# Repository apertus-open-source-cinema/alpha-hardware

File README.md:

alpha-hardware
==============

Axiom Alpha prototype hardware source files (electronic schematics, documentation, PCB layouts, etc.)

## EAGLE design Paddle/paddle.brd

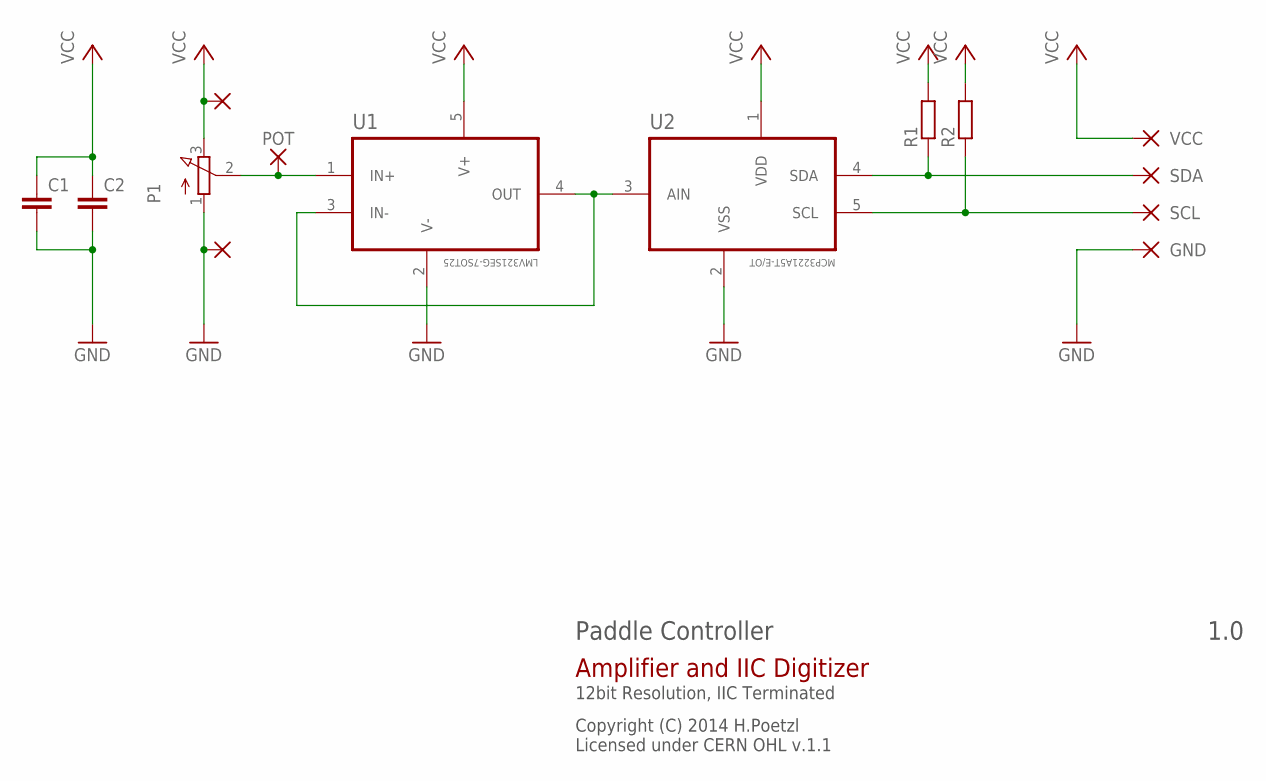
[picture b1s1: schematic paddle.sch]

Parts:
C1, C2: C-EUC1206K; C1206K
GND: SMD2; SMD1,27-2,54
P1: 3RP/1610N
POT: SMD2; SMD1,27-2,54
R1: R-EU_0204/7; 0204/7
R2: R-EU_0204/5; 0204/5
SCL: SMD2; SMD1,27-2,54
SDA: SMD2; SMD1,27-2,54
U1: LMV321SEG-7SOT25; SOT95P280X145-5N
U2: MCP3221A5T-E/OT; SOT95P270X145-5N
VCC, VCC1, VCC2: SMD2; SMD1,27-2,54

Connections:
GND: C1.2, C2.2, GND.1, P1.1 (A), U1.2 (V-), U2.2 (VSS), VCC2.1
unnamed: U1.3 (IN-), U1.4 (OUT), U2.3 (AIN)
POT: P1.2 (S), POT.1, U1.1 (IN+)
SCL: R2.1, SCL.1, U2.5 (SCL)
SDA: R1.1, SDA.1, U2.4 (SDA)
VCC: C1.1, C2.1, P1.3 (E), R1.2, R2.2, U1.5 (V+), U2.1 (VDD), VCC.1, VCC1.1

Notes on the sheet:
Paddle Controller
Copyright (C) 2014 H.Poetzl Licensed under CERN OHL v.1.1
Amplifier and IIC Digitizer
12bit Resolution, IIC Terminated

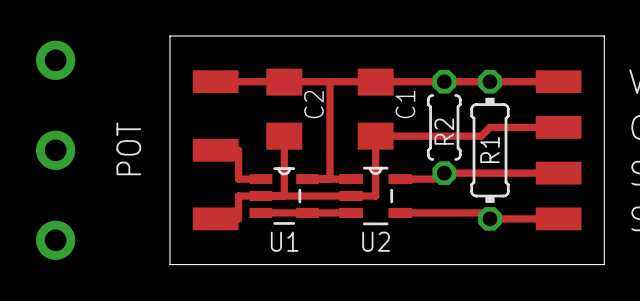
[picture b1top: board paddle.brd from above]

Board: 2 copper layers, 24.1 x 12.7 mm, 14 parts (1 on the bottom side), 6 nets.

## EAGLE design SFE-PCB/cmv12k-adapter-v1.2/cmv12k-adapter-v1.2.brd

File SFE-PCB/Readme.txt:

=========
= About = 
=========

ExpressPCB PCB (*.pcb) and schematic (*.sch) files (http://www.expresspcb.com/)
Sensor Front End for the apertus° Axiom Alpha camera prototype: http://axiom.apertus.org/index.php?site=alpha

===========
= Authors =
===========

Stuart  Allman - contact through apertus° contact form: http://apertus.org/contact
Sebastian Pichelhofer - contact through apertus° contact form: http://apertus.org/contact

========
= TODO =
========

-) double check the footprints (FMC connector seems correct, but the sensor socket should be checked)
-) turn off "snap to grid" feature and manually adjust the spacing on the LVDS pairs as per the schematic note. 
I usually do this by placing a silkscreen trace of the correct width and aligning the traces at the edge of the silkscreen.
-) check dimensions of the PCB and if we will get into the way of anything on the zedboard

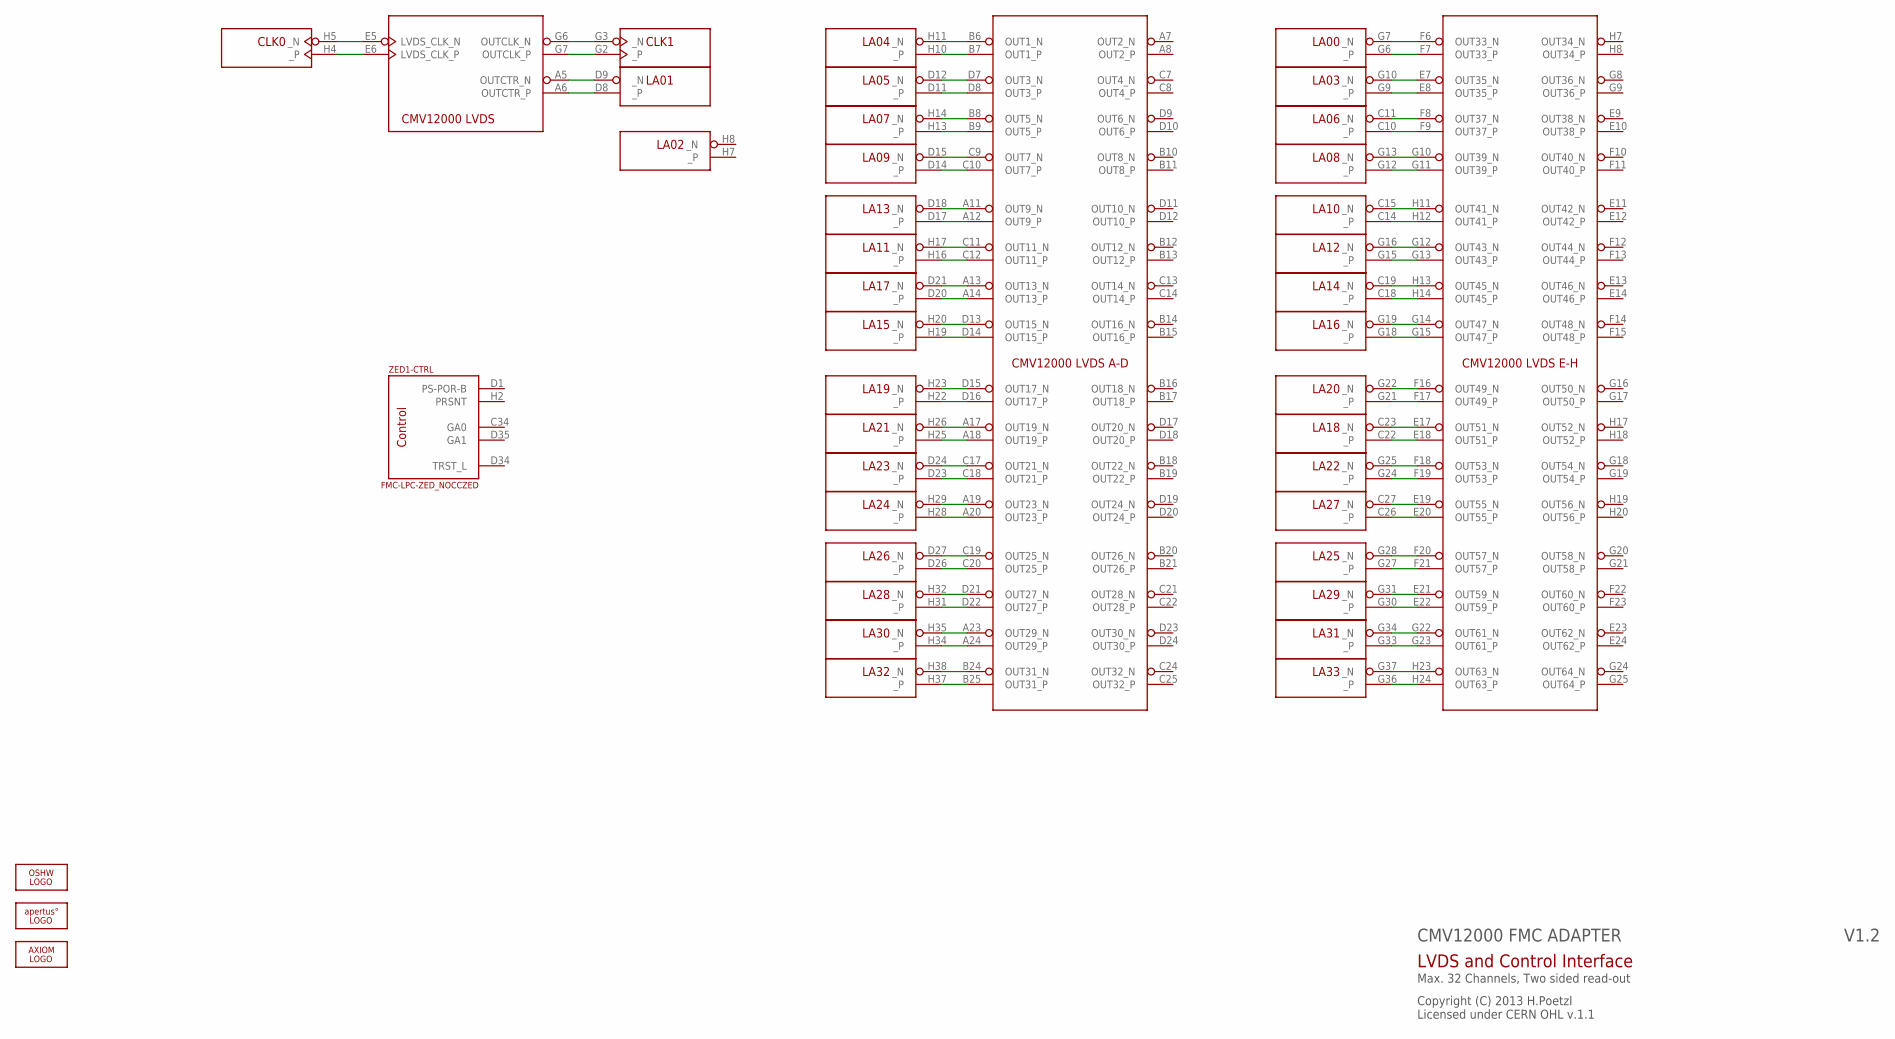
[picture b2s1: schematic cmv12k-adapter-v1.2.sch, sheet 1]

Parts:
LOGO1: OSHW_LOGO_FILLX0100-NT; OSHW_FILLX100_NOTEXT
SOCKET: CMV12000ANDON+LM; 10-30-07-237-400T4+LM
U$5: APERTUS_LOGO334X100; APERTUS_LOGO_334X100
U$13: AXIOM_LOGO525X80; AXIOM_LOGO_525X80
ZED1: FMC-LPC-ZED_NOCCZED; ASP-134604-01-ZED

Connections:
CLK0_N: SOCKET.E5 (LVDS_CLK_N), ZED1.H5 (_N)
CLK0_P: SOCKET.E6 (LVDS_CLK_P), ZED1.H4 (_P)
CLK1_N: SOCKET.G6 (OUTCLK_N), ZED1.G3 (_N)
CLK1_P: SOCKET.G7 (OUTCLK_P), ZED1.G2 (_P)
LA00_N: SOCKET.F6 (OUT33_N), ZED1.G7 (_N)
LA00_P: SOCKET.F7 (OUT33_P), ZED1.G6 (_P)
LA01_N: SOCKET.A5 (OUTCTR_N), ZED1.D9 (_N)
LA01_P: SOCKET.A6 (OUTCTR_P), ZED1.D8 (_P)
LA03_N: SOCKET.E7 (OUT35_N), ZED1.G10 (_N)
LA03_P: SOCKET.E8 (OUT35_P), ZED1.G9 (_P)
LA04_N: SOCKET.B6 (OUT1_N), ZED1.H11 (_N)
LA04_P: SOCKET.B7 (OUT1_P), ZED1.H10 (_P)
LA05_N: SOCKET.D7 (OUT3_N), ZED1.D12 (_N)
LA05_P: SOCKET.D8 (OUT3_P), ZED1.D11 (_P)
LA06_N: SOCKET.F8 (OUT37_N), ZED1.C11 (_N)
LA06_P: SOCKET.F9 (OUT37_P), ZED1.C10 (_P)
LA07_N: SOCKET.B8 (OUT5_N), ZED1.H14 (_N)
LA07_P: SOCKET.B9 (OUT5_P), ZED1.H13 (_P)
LA08_N: SOCKET.G10 (OUT39_N), ZED1.G13 (_N)
LA08_P: SOCKET.G11 (OUT39_P), ZED1.G12 (_P)
LA09_N: SOCKET.C9 (OUT7_N), ZED1.D15 (_N)
LA09_P: SOCKET.C10 (OUT7_P), ZED1.D14 (_P)
LA10_N: SOCKET.H11 (OUT41_N), ZED1.C15 (_N)
LA10_P: SOCKET.H12 (OUT41_P), ZED1.C14 (_P)
LA11_N: SOCKET.C11 (OUT11_N), ZED1.H17 (_N)
LA11_P: SOCKET.C12 (OUT11_P), ZED1.H16 (_P)
LA12_N: SOCKET.G12 (OUT43_N), ZED1.G16 (_N)
LA12_P: SOCKET.G13 (OUT43_P), ZED1.G15 (_P)
LA13_N: SOCKET.A11 (OUT9_N), ZED1.D18 (_N)
LA13_P: SOCKET.A12 (OUT9_P), ZED1.D17 (_P)
LA14_N: SOCKET.H13 (OUT45_N), ZED1.C19 (_N)
LA14_P: SOCKET.H14 (OUT45_P), ZED1.C18 (_P)
LA15_N: SOCKET.D13 (OUT15_N), ZED1.H20 (_N)
LA15_P: SOCKET.D14 (OUT15_P), ZED1.H19 (_P)
LA16_N: SOCKET.G14 (OUT47_N), ZED1.G19 (_N)
LA16_P: SOCKET.G15 (OUT47_P), ZED1.G18 (_P)
LA17_N: SOCKET.A13 (OUT13_N), ZED1.D21 (_N)
LA17_P: SOCKET.A14 (OUT13_P), ZED1.D20 (_P)
LA18_N: SOCKET.E17 (OUT51_N), ZED1.C23 (_N)
LA18_P: SOCKET.E18 (OUT51_P), ZED1.C22 (_P)
LA19_N: SOCKET.D15 (OUT17_N), ZED1.H23 (_N)
LA19_P: SOCKET.D16 (OUT17_P), ZED1.H22 (_P)
LA20_N: SOCKET.F16 (OUT49_N), ZED1.G22 (_N)
LA20_P: SOCKET.F17 (OUT49_P), ZED1.G21 (_P)
LA21_N: SOCKET.A17 (OUT19_N), ZED1.H26 (_N)
LA21_P: SOCKET.A18 (OUT19_P), ZED1.H25 (_P)
LA22_N: SOCKET.F18 (OUT53_N), ZED1.G25 (_N)
LA22_P: SOCKET.F19 (OUT53_P), ZED1.G24 (_P)
LA23_N: SOCKET.C17 (OUT21_N), ZED1.D24 (_N)
LA23_P: SOCKET.C18 (OUT21_P), ZED1.D23 (_P)
LA24_N: SOCKET.A19 (OUT23_N), ZED1.H29 (_N)
LA24_P: SOCKET.A20 (OUT23_P), ZED1.H28 (_P)
LA25_N: SOCKET.F20 (OUT57_N), ZED1.G28 (_N)
LA25_P: SOCKET.F21 (OUT57_P), ZED1.G27 (_P)
LA26_N: SOCKET.C19 (OUT25_N), ZED1.D27 (_N)
LA26_P: SOCKET.C20 (OUT25_P), ZED1.D26 (_P)
LA27_N: SOCKET.E19 (OUT55_N), ZED1.C27 (_N)
LA27_P: SOCKET.E20 (OUT55_P), ZED1.C26 (_P)
LA28_N: SOCKET.D21 (OUT27_N), ZED1.H32 (_N)
LA28_P: SOCKET.D22 (OUT27_P), ZED1.H31 (_P)
LA29_N: SOCKET.E21 (OUT59_N), ZED1.G31 (_N)
LA29_P: SOCKET.E22 (OUT59_P), ZED1.G30 (_P)
LA30_N: SOCKET.A23 (OUT29_N), ZED1.H35 (_N)
LA30_P: SOCKET.A24 (OUT29_P), ZED1.H34 (_P)
LA31_N: SOCKET.G22 (OUT61_N), ZED1.G34 (_N)
LA31_P: SOCKET.G23 (OUT61_P), ZED1.G33 (_P)
LA32_N: SOCKET.B24 (OUT31_N), ZED1.H38 (_N)
LA32_P: SOCKET.B25 (OUT31_P), ZED1.H37 (_P)
LA33_N: SOCKET.H23 (OUT63_N), ZED1.G37 (_N)
LA33_P: SOCKET.H24 (OUT63_P), ZED1.G36 (_P)

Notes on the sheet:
CMV12000 FMC ADAPTER
Copyright (C) 2013 H.Poetzl Licensed under CERN OHL v.1.1
LVDS and Control Interface
Max. 32 Channels, Two sided read-out

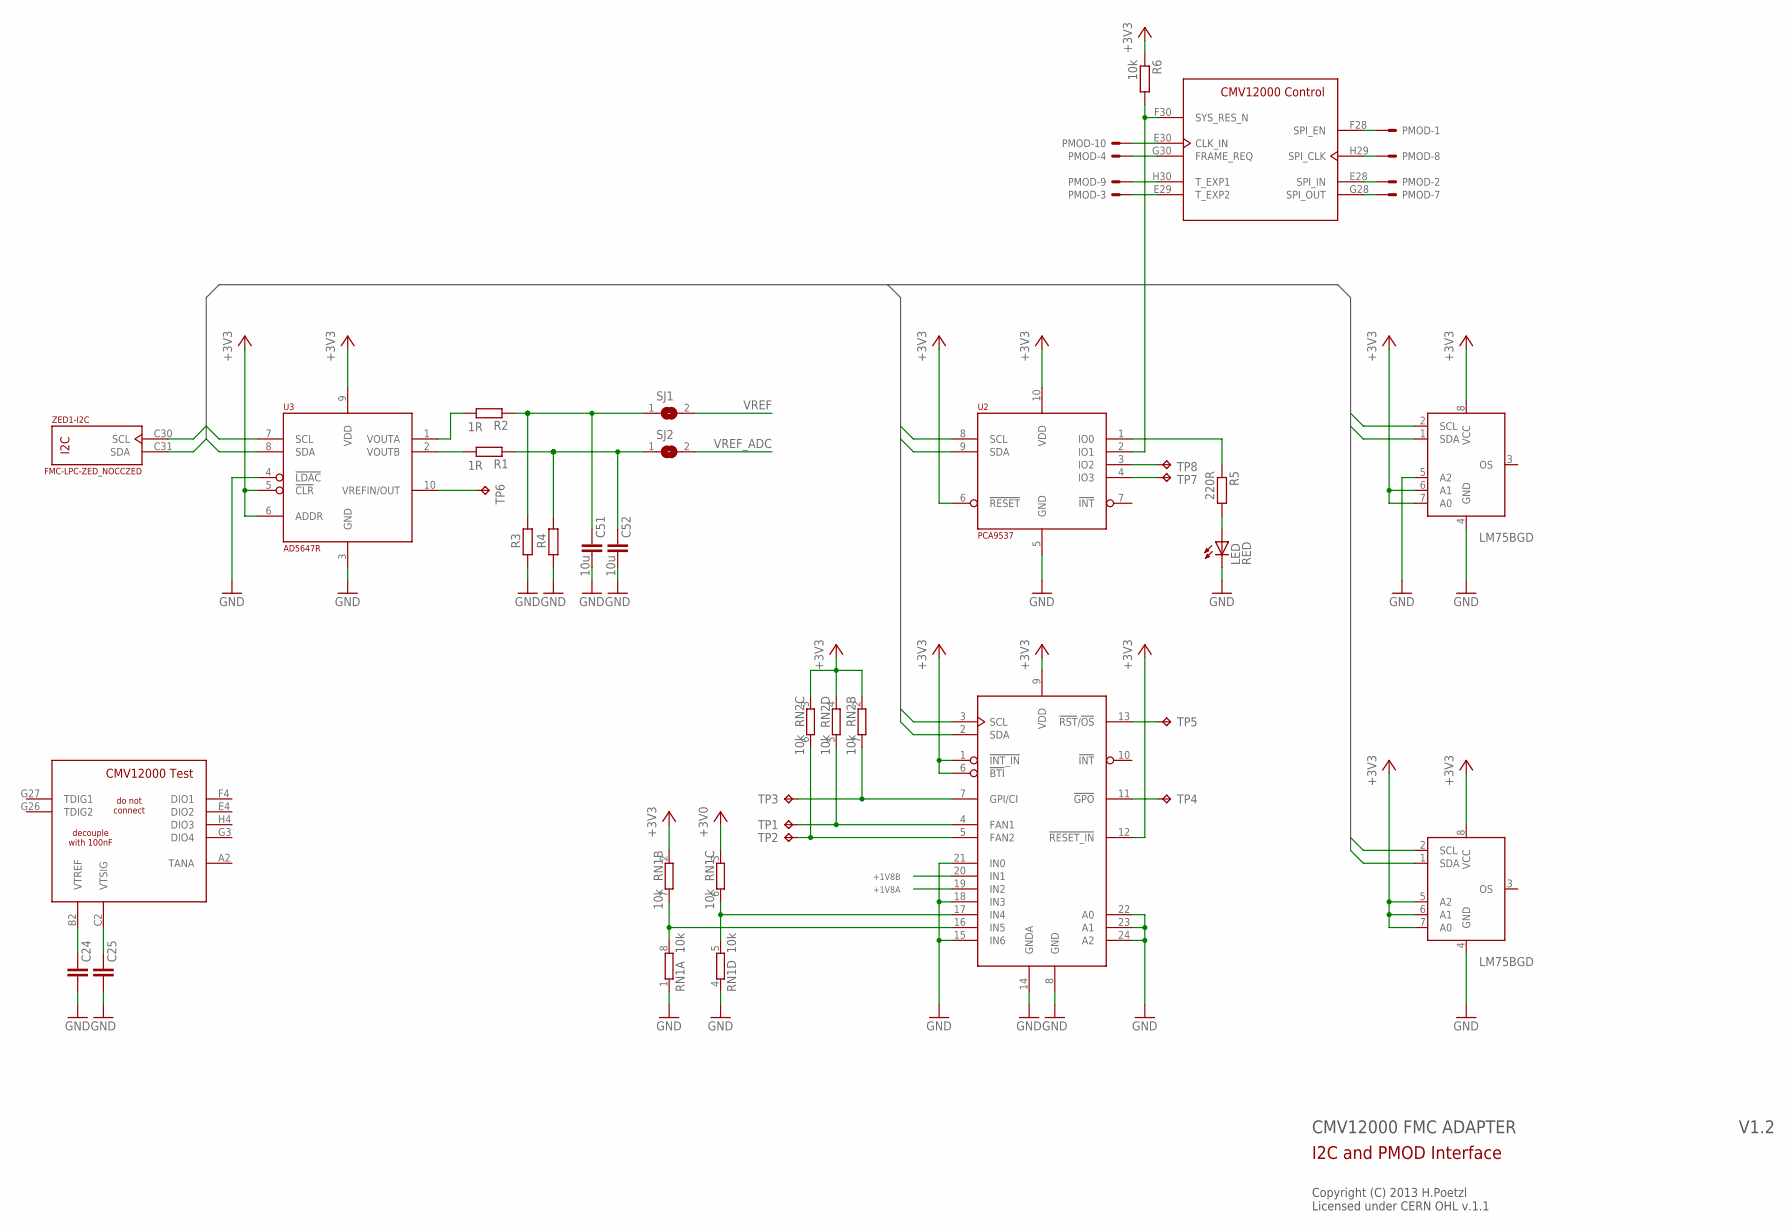
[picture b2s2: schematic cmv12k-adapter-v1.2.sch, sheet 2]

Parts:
C24, C25: 100n; C0402
C51, C52: 10u; C0603K
LED: RED; CHIP-LED0603
PMOD: PMOD-8; 2X04/90/2MM
R1, R2: 1R; R0402
R3, R4: R-EU_R0402; R0402
R5: 220R; R0402
R6: 10k; R0402
RN1, RN2: 10k; EXBV8V
SJ1, SJ2: SJ
SOCKET: CMV12000ANDON+LM; 10-30-07-237-400T4+LM
TP1, TP2, TP3, TP4, TP5, TP6, TP7, TP8: TPB1,27; B1,27
U1: LM96080; TSSOP24
U2: PCA9537; TSSOP-10
U3: AD5647R; SOP50P490X110-10N
U4, U5: LM75BGD; SOT996-2/3
ZED1: FMC-LPC-ZED_NOCCZED; ASP-134604-01-ZED

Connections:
#GPO: TP4.TP, U1.11 (!GPO)
#RST/OS: TP5.TP, U1.13 (!RST!/!OS!)
+1V8A: U1.19 (IN2); also elsewhere on the board
+1V8B: U1.20 (IN1); also elsewhere on the board
+3V0: RN1.3 (1); also elsewhere on the board
+3V3: R6.1, RN1.2 (1), RN2.2 (1), RN2.3 (1), RN2.4 (1), U1.1 (!INT_IN), U1.6 (!BTI), U1.9 (VDD), U1.12 (!RESET_IN), U2.6 (!RESET), U2.10 (VDD), U3.5 (!CLR), U3.6 (ADDR), U3.9 (VDD), U4.6 (A1), U4.7 (A0), U4.8 (VCC), U5.5 (A2), U5.6 (A1), U5.7 (A0), U5.8 (VCC); also elsewhere on the board
CLK_IN: PMOD.10, SOCKET.E30 (CLK_IN)
FAN1: RN2.5 (2), TP1.TP, U1.4 (FAN1)
FAN2: RN2.6 (2), TP2.TP, U1.5 (FAN2)
FRAME_REQ: PMOD.4, SOCKET.G30 (FRAME_REQ)
GND: C24.2, C25.2, C51.2, C52.2, LED.C, R3.2, R4.2, RN1.1, RN1.4 (1), U1.8 (GND), U1.14 (GNDA), U1.15 (IN6), U1.18 (IN3), U1.21 (IN0), U1.22 (A0), U1.23 (A1), U1.24 (A2), U2.5 (GND), U3.3 (GND), U3.4 (!LDAC), U4.4 (GND), U4.5 (A2), U5.4 (GND); also elsewhere on the board
GPI/CI: RN2.7 (2), TP3.TP, U1.7 (GPI/CI)
IN4: RN1.5 (2), RN1.6 (2), U1.17 (IN4)
IN5: RN1.7 (2), RN1.8 (2), U1.16 (IN5)
IO0: R5.1, U2.1 (IO0)
IO1: R6.2, SOCKET.F30 (SYS_RES_N), U2.2 (IO1)
IO2: TP8.TP, U2.3 (IO2)
IO3: TP7.TP, U2.4 (IO3)
unnamed: C24.1, SOCKET.B2 (VTREF)
unnamed: C25.1, SOCKET.C2 (VTSIG)
unnamed: LED.A, R5.2
SCL: U1.3 (SCL), U2.8 (SCL), U3.7 (SCL), U4.2 (SCL), U5.2 (SCL), ZED1.C30 (SCL)
SDA: U1.2 (SDA), U2.9 (SDA), U3.8 (SDA), U4.1 (SDA), U5.1 (SDA), ZED1.C31 (SDA)
SPI_CLK: PMOD.8, SOCKET.H29 (SPI_CLK)
SPI_EN: PMOD.1, SOCKET.F28 (SPI_EN)
SPI_IN: PMOD.2, SOCKET.E28 (SPI_IN)
SPI_OUT: PMOD.7, SOCKET.G28 (SPI_OUT)
T_EXP1: PMOD.9, SOCKET.H30 (T_EXP1)
T_EXP2: PMOD.3, SOCKET.E29 (T_EXP2)
VOUTA: R2.2, U3.1 (VOUTA)
VOUTB: R1.2, U3.2 (VOUTB)
VREF: SJ1.2; also elsewhere on the board
VREFIN/OUT: TP6.TP, U3.10 (VREFIN/OUT)
VREF_ADC: SJ2.2; also elsewhere on the board
_VREF: C51.1, R2.1, R3.1, SJ1.1
_VREF_ADC: C52.1, R1.1, R4.1, SJ2.1

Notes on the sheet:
CMV12000 FMC ADAPTER
Copyright (C) 2013 H.Poetzl Licensed under CERN OHL v.1.1
I2C and PMOD Interface

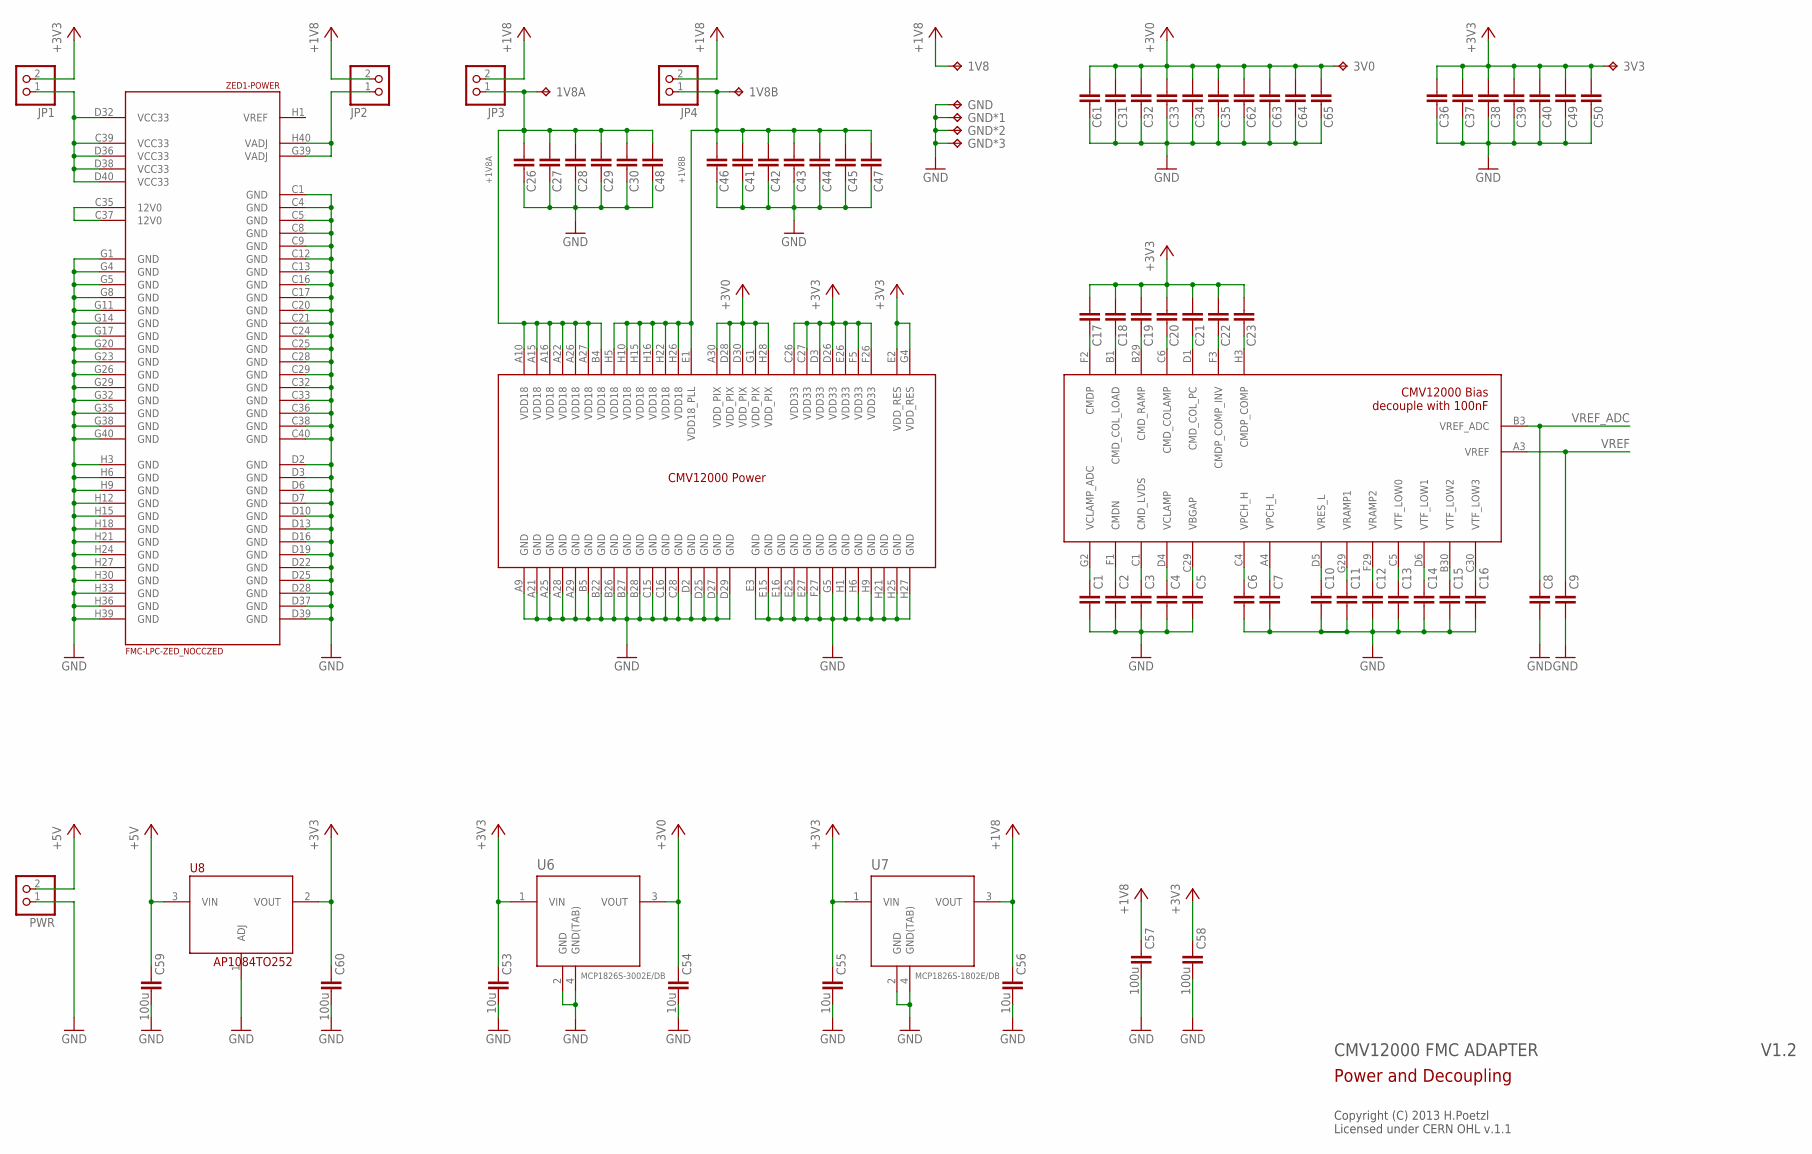
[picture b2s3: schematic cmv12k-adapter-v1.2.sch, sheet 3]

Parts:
1V8, 1V8A, 1V8B, 3V0, 3V3: TPB1,27; B1,27
C1, C2, C3, C4, C5, C6, C7, C8, C9, C10, C11, C12, C13, C14, C15, C16, C17, C18, C19, C20, C21, C22, C23, C26, C27, C28, C29, C30, C31, C32, C33, C34, C35, C36, C37, C38, C39, C40, C41, C42, C43, C44, C45, C46, C47, C48, C49, C50: 100n; C0402
C53, C54, C55, C56: 10u; C0603K
C57, C58: 100u; C1210
C59, C60: 100u; C1210K
C61: 22µ; C0805
C62, C63, C64, C65: 4µ7; C0402
GND: TPB1,27; B1,27
GND*1, GND*2, GND*3: TPB1,27; B1,27
JP1, JP2, JP3, JP4: PINHD-1X02_2.54-S; 1X02-S
PWR: PINHD-1X02_2.54-S; 1X02-S
SOCKET: CMV12000ANDON+LM; 10-30-07-237-400T4+LM
U6: MCP1826S-3002E/DB; SOT230P700X180-4N
U7: MCP1826S-1802E/DB; SOT230P700X180-4N
U8: AP1084TO252; TO252
ZED1: FMC-LPC-ZED_NOCCZED; ASP-134604-01-ZED

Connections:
+1V8: 1V8.TP, C56.1, C57.1, JP2.2, JP3.2, JP4.2, U7.3 (VOUT)
+1V8A: 1V8A.TP, C26.1, C27.1, C28.1, C29.1, C30.1, C48.1, JP3.1, SOCKET.A10 (VDD18), SOCKET.A15 (VDD18), SOCKET.A16 (VDD18), SOCKET.A22 (VDD18), SOCKET.A26 (VDD18), SOCKET.A27 (VDD18), SOCKET.B4 (VDD18); also elsewhere on the board
+1V8B: 1V8B.TP, C41.1, C42.1, C43.1, C44.1, C45.1, C46.1, C47.1, JP4.1, SOCKET.E1 (VDD18_PLL), SOCKET.H5 (VDD18), SOCKET.H10 (VDD18), SOCKET.H15 (VDD18), SOCKET.H16 (VDD18), SOCKET.H22 (VDD18), SOCKET.H26 (VDD18); also elsewhere on the board
+3V0: 3V0.TP, C31.1, C32.1, C33.1, C34.1, C35.1, C54.1, C61.1, C62.1, C63.1, C64.1, C65.1, SOCKET.A30 (VDD_PIX), SOCKET.D28 (VDD_PIX), SOCKET.D30 (VDD_PIX), SOCKET.G1 (VDD_PIX), SOCKET.H28 (VDD_PIX), U6.3 (VOUT); also elsewhere on the board
+3V3: 3V3.TP, C17.1, C18.1, C19.1, C20.1, C21.1, C22.1, C23.1, C36.1, C37.1, C38.1, C39.1, C40.1, C49.1, C50.1, C53.1, C55.1, C58.1, C60.1, JP1.2, SOCKET.C26 (VDD33), SOCKET.C27 (VDD33), SOCKET.D3 (VDD33), SOCKET.D26 (VDD33), SOCKET.E2 (VDD_RES), SOCKET.E26 (VDD33), SOCKET.F5 (VDD33), SOCKET.F26 (VDD33), SOCKET.G4 (VDD_RES), U6.1 (VIN), U7.1 (VIN), U8.2 (VOUT); also elsewhere on the board
+5V: C59.1, PWR.2, U8.3 (VIN)
GND: C1.2, C2.2, C3.2, C4.2, C5.2, C6.2, C7.2, C8.2, C9.2, C10.2, C11.2, C12.2, C13.2, C14.2, C15.2, C16.2, C26.2, C27.2, C28.2, C29.2, C30.2, C31.2, C32.2, C33.2, C34.2, C35.2, C36.2, C37.2, C38.2, C39.2, C40.2, C41.2, C42.2, C43.2, C44.2, C45.2, C46.2, C47.2, C48.2, C49.2, C50.2, C53.2, C54.2, C55.2, C56.2, C57.2, C58.2, C59.2, C60.2, C61.2, C62.2, C63.2, C64.2, C65.2, GND.TP, GND*1.TP, GND*2.TP, GND*3.TP, PWR.1, SOCKET.A9 (GND), SOCKET.A21 (GND), SOCKET.A25 (GND), SOCKET.A28 (GND), SOCKET.A29 (GND), SOCKET.B5 (GND), SOCKET.B22 (GND), SOCKET.B26 (GND), SOCKET.B27 (GND), SOCKET.B28 (GND), SOCKET.C15 (GND), SOCKET.C16 (GND), SOCKET.C28 (GND), SOCKET.D2 (GND), SOCKET.D25 (GND), SOCKET.D27 (GND), SOCKET.D29 (GND), SOCKET.E3 (GND), SOCKET.E15 (GND), SOCKET.E16 (GND), SOCKET.E25 (GND), SOCKET.E27 (GND), SOCKET.F27 (GND), SOCKET.G5 (GND), SOCKET.H1 (GND), SOCKET.H6 (GND), SOCKET.H9 (GND), SOCKET.H21 (GND), SOCKET.H25 (GND), SOCKET.H27 (GND), U6.2 (GND), U6.4 (GND(TAB)), U7.2 (GND), U7.4 (GND(TAB)), U8.1 (ADJ), ZED1.C1 (GND), ZED1.C4 (GND), ZED1.C5 (GND), ZED1.C8 (GND), ZED1.C9 (GND), ZED1.C12 (GND), ZED1.C13 (GND), ZED1.C16 (GND), ZED1.C17 (GND), ZED1.C20 (GND), ZED1.C21 (GND), ZED1.C24 (GND), ZED1.C25 (GND), ZED1.C28 (GND), ZED1.C29 (GND), ZED1.C32 (GND), ZED1.C33 (GND), ZED1.C36 (GND), ZED1.C38 (GND), ZED1.C40 (GND), ZED1.D2 (GND), ZED1.D3 (GND), ZED1.D6 (GND), ZED1.D7 (GND), ZED1.D10 (GND), ZED1.D13 (GND), ZED1.D16 (GND), ZED1.D19 (GND), ZED1.D22 (GND), ZED1.D25 (GND), ZED1.D28 (GND), ZED1.D37 (GND), ZED1.D39 (GND), ZED1.G1 (GND), ZED1.G4 (GND), ZED1.G5 (GND), ZED1.G8 (GND), ZED1.G11 (GND), ZED1.G14 (GND), ZED1.G17 (GND), ZED1.G20 (GND), ZED1.G23 (GND), ZED1.G26 (GND), ZED1.G29 (GND), ZED1.G32 (GND), ZED1.G35 (GND), ZED1.G38 (GND), ZED1.G40 (GND), ZED1.H3 (GND), ZED1.H6 (GND), ZED1.H9 (GND), ZED1.H12 (GND), ZED1.H15 (GND), ZED1.H18 (GND), ZED1.H21 (GND), ZED1.H24 (GND), ZED1.H27 (GND), ZED1.H30 (GND), ZED1.H33 (GND), ZED1.H36 (GND), ZED1.H39 (GND); also elsewhere on the board
unnamed: C17.2, SOCKET.F2 (CMDP)
unnamed: C18.2, SOCKET.B1 (CMD_COL_LOAD)
unnamed: C19.2, SOCKET.B29 (CMD_RAMP)
unnamed: C20.2, SOCKET.C6 (CMD_COLAMP)
unnamed: C21.2, SOCKET.D1 (CMD_COL_PC)
unnamed: C22.2, SOCKET.F3 (CMDP_COMP_INV)
unnamed: C23.2, SOCKET.H3 (CMDP_COMP)
unnamed: C1.1, SOCKET.G2 (VCLAMP_ADC)
unnamed: C2.1, SOCKET.F1 (CMDN)
unnamed: C3.1, SOCKET.C1 (CMD_LVDS)
unnamed: C4.1, SOCKET.D4 (VCLAMP)
unnamed: C5.1, SOCKET.C29 (VBGAP)
unnamed: C6.1, SOCKET.C4 (VPCH_H)
unnamed: C7.1, SOCKET.A4 (VPCH_L)
unnamed: C10.1, SOCKET.D5 (VRES_L)
unnamed: C11.1, SOCKET.G29 (VRAMP1)
unnamed: C12.1, SOCKET.F29 (VRAMP2)
unnamed: C13.1, SOCKET.C5 (VTF_LOW0)
unnamed: C14.1, SOCKET.D6 (VTF_LOW1)
unnamed: C15.1, SOCKET.B30 (VTF_LOW2)
unnamed: C16.1, SOCKET.C30 (VTF_LOW3)
unnamed: ZED1.C35 (12V0), ZED1.C37 (12V0)
unnamed: JP1.1, ZED1.C39 (VCC33), ZED1.D32 (VCC33), ZED1.D36 (VCC33), ZED1.D38 (VCC33), ZED1.D40 (VCC33)
unnamed: JP2.1, ZED1.G39 (VADJ), ZED1.H40 (VADJ)
VREF: C9.1, SOCKET.A3 (VREF); also elsewhere on the board
VREF_ADC: C8.1, SOCKET.B3 (VREF_ADC); also elsewhere on the board

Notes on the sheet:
CMV12000 FMC ADAPTER
Copyright (C) 2013 H.Poetzl Licensed under CERN OHL v.1.1
Power and Decoupling

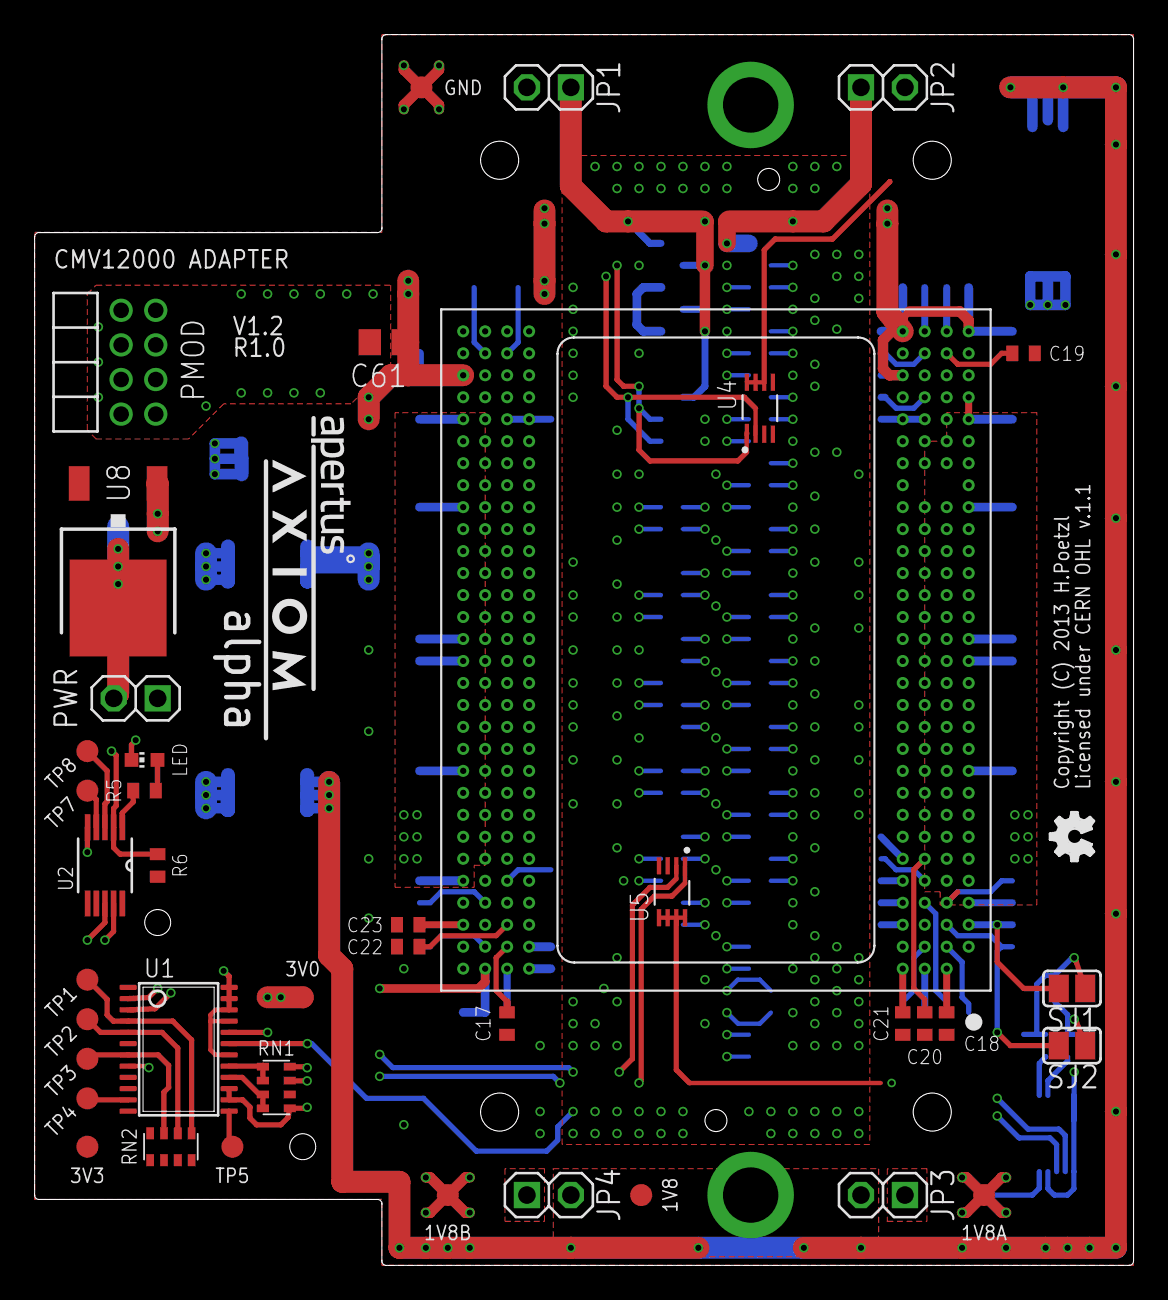
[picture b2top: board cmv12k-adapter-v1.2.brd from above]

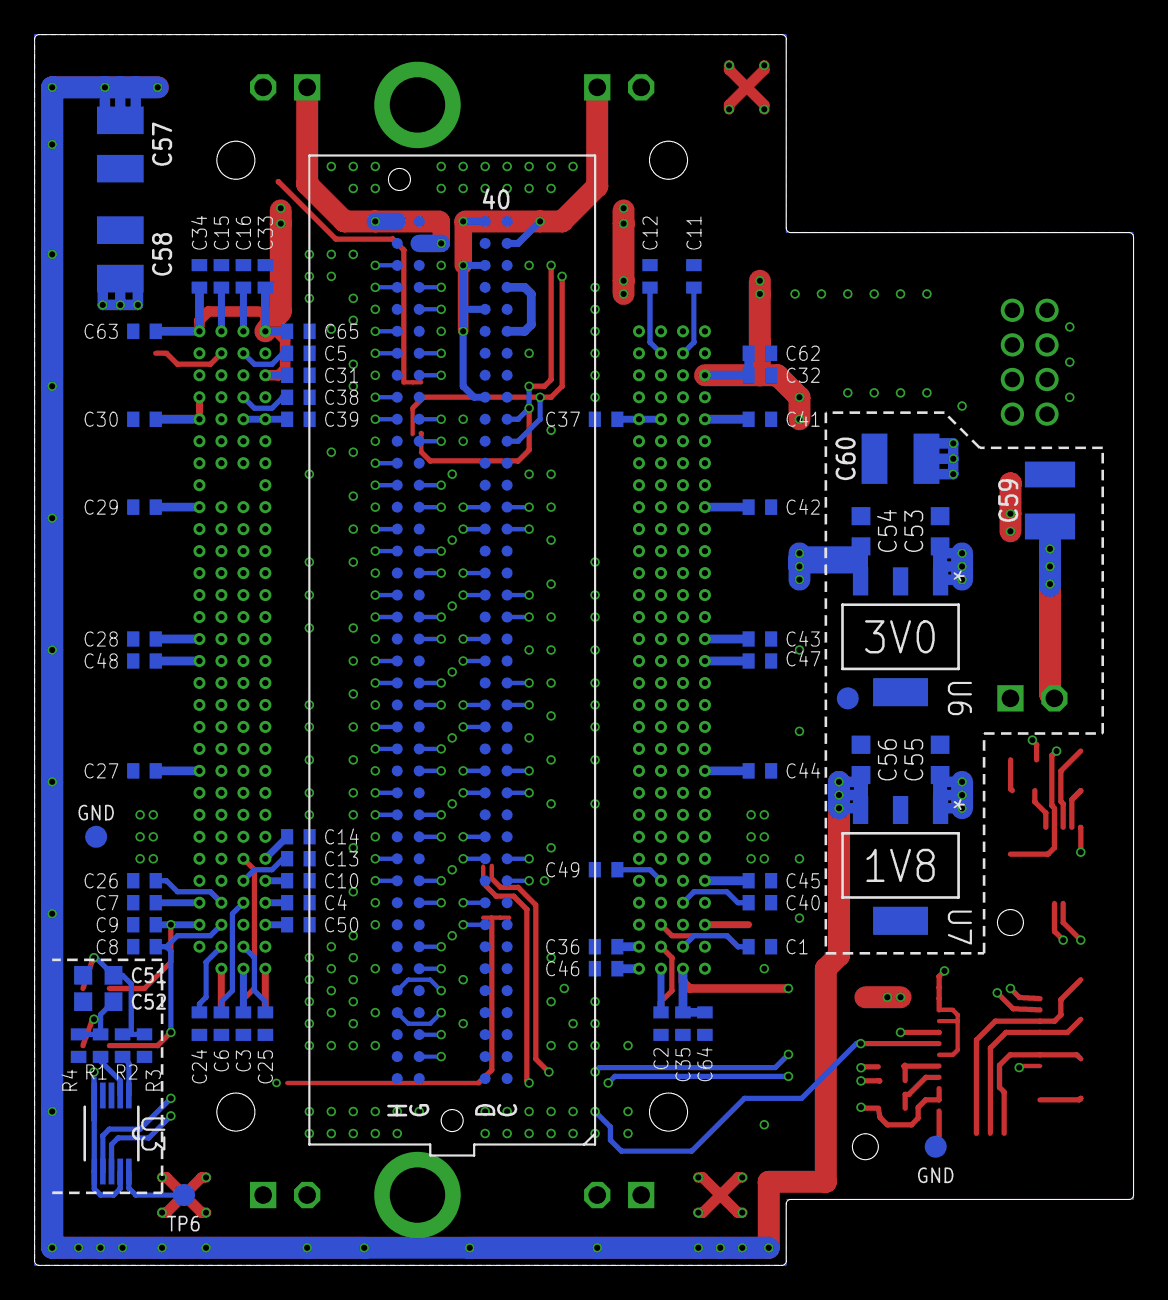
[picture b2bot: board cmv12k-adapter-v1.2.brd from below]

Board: 4 copper layers, 63.5 x 71.1 mm, 112 parts (68 on the bottom side), 132 nets.

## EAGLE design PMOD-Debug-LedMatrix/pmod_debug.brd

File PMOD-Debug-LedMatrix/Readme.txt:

About
---------
A very small PCB sporting 64 LEDs that connect to most FPGA development boards (like the Zedboard) with a PMOD interface
This PCB provides an easy way to debug FPGA logic with just 8 digital lines and a 4-to-16 line decoder with minimal interface logic required in the FPGA side (PL).

Filetypes
---------
Eagle Schematic and Board Design (XML)

License
---------
CERN Open Hardware License 1.1
http://www.ohwr.org/attachments/735/CERNOHLv1_1.txt

Author
---------
Herbert Poetzl - herbert@13thfloor.at

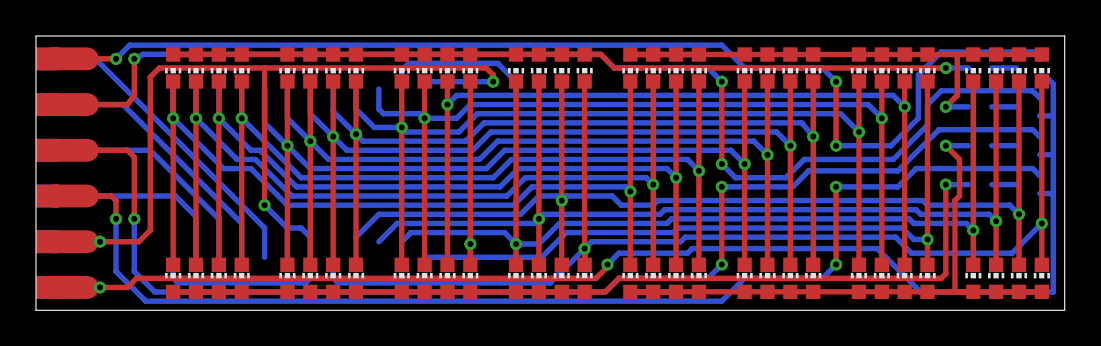
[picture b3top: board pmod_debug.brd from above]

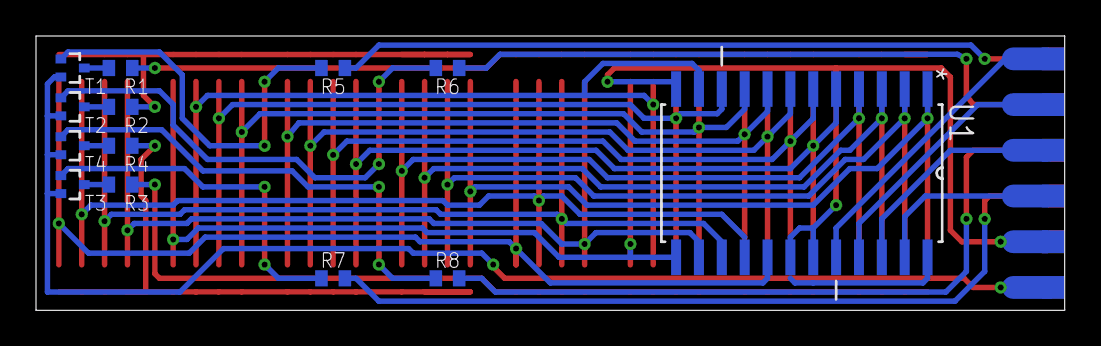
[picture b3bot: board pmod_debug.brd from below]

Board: 2 copper layers, 57.1 x 15.2 mm, 89 parts (19 on the bottom side), 38 nets.

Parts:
LED1, LED2, LED3, LED4, LED5, LED6, LED7, LED8, LED9, LED10, LED11, LED12, LED13, LED14, LED15, LED16, LED17, LED18, LED19, LED20, LED21, LED22, LED23, LED24, LED25, LED26, LED27, LED28, LED29, LED30, LED31, LED32, LED33, LED34, LED35, LED36, LED37, LED38, LED39, LED40, LED41, LED42, LED43, LED44, LED45, LED46, LED47, LED48, LED49, LED50, LED51, LED52, LED53, LED54, LED55, LED56, LED57, LED58, LED59, LED60, LED61, LED62, LED63, LED64: CHIP-LED0603
PAD1, PAD2, PAD3, PAD4, PAD5, PAD6, PAD7, PAD8, PAD9, PAD10, PAD11, PAD12: SMD1.27-3.175HR
R1, R2, R3, R4: 560R; R0402
R5, R6, R7, R8: 220R; R0402
T1, T2, T3, T4: BSS84AKT; SOT416
U1: CD74HC154M; SOIC127P1030X265-24N

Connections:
+3V3: PAD6.1, PAD12.1, T1.2, T2.2, T3.2, T4.2, U1.24
C0: LED1.C, LED17.C, LED33.C, LED49.C, U1.1
C1: LED2.C, LED18.C, LED34.C, LED50.C, U1.2
C2: LED3.C, LED19.C, LED35.C, LED51.C, U1.3
C3: LED4.C, LED20.C, LED36.C, LED52.C, U1.4
C4: LED5.C, LED21.C, LED37.C, LED53.C, U1.5
C5: LED6.C, LED22.C, LED38.C, LED54.C, U1.6
C6: LED7.C, LED23.C, LED39.C, LED55.C, U1.7
C7: LED8.C, LED24.C, LED40.C, LED56.C, U1.8
C8: LED9.C, LED25.C, LED41.C, LED57.C, U1.9
C9: LED10.C, LED26.C, LED42.C, LED58.C, U1.10
C10: LED11.C, LED27.C, LED43.C, LED59.C, U1.11
C11: LED12.C, LED28.C, LED44.C, LED60.C, U1.13
C12: LED13.C, LED29.C, LED45.C, LED61.C, U1.14
C13: LED14.C, LED30.C, LED46.C, LED62.C, U1.15
C14: LED15.C, LED31.C, LED47.C, LED63.C, U1.16
C15: LED16.C, LED32.C, LED48.C, LED64.C, U1.17
GND: PAD5.1, PAD11.1, U1.12, U1.18, U1.19
unnamed: LED1.A, LED2.A, LED3.A, LED4.A, LED5.A, LED6.A, LED7.A, LED8.A, LED9.A, LED10.A, LED11.A, LED12.A, LED13.A, LED14.A, LED15.A, LED16.A, R1.1
unnamed: LED17.A, LED18.A, LED19.A, LED20.A, LED21.A, LED22.A, LED23.A, LED24.A, LED25.A, LED26.A, LED27.A, LED28.A, LED29.A, LED30.A, LED31.A, LED32.A, R2.1
unnamed: LED33.A, LED34.A, LED35.A, LED36.A, LED37.A, LED38.A, LED39.A, LED40.A, LED41.A, LED42.A, LED43.A, LED44.A, LED45.A, LED46.A, LED47.A, LED48.A, R3.1
unnamed: LED49.A, LED50.A, LED51.A, LED52.A, LED53.A, LED54.A, LED55.A, LED56.A, LED57.A, LED58.A, LED59.A, LED60.A, LED61.A, LED62.A, LED63.A, LED64.A, R4.1
unnamed: R4.2, T4.3
unnamed: R3.2, T3.3
unnamed: R1.2, T1.3
unnamed: R2.2, T2.3
unnamed: R8.1, T4.1
unnamed: R7.1, T3.1
unnamed: R5.1, T1.1
unnamed: R6.1, T2.1
unnamed: PAD10.1, U1.23
unnamed: PAD9.1, U1.22
unnamed: PAD8.1, U1.21
unnamed: PAD7.1, U1.20
unnamed: PAD1.1, R5.2
unnamed: PAD2.1, R6.2
unnamed: PAD3.1, R8.2
unnamed: PAD4.1, R7.2

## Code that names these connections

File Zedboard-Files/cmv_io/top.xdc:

create_clock -name clk_100 -period 10 -waveform {0 5} [get_ports clk_100]
set_property PACKAGE_PIN Y9 [get_ports clk_100]
set_property IOSTANDARD LVCMOS33 [get_ports clk_100]

set_property PACKAGE_PIN Y16 [get_ports i2c0_sda]
set_property PACKAGE_PIN AA18 [get_ports i2c0_scl]

set_property IOSTANDARD LVCMOS33 [get_ports i2c0_*]

set_property PACKAGE_PIN U7 [get_ports i2c1_sda]
set_property PACKAGE_PIN R7 [get_ports i2c1_scl]

set_property IOSTANDARD LVCMOS33 [get_ports i2c1_*]

set_property PACKAGE_PIN V12 [get_ports spi_en]
set_property PACKAGE_PIN W11 [get_ports spi_clk]
set_property PACKAGE_PIN W10 [get_ports spi_in]
set_property PACKAGE_PIN W12 [get_ports spi_out]

set_property IOSTANDARD LVCMOS33 [get_ports spi_*]

set_property PACKAGE_PIN T22 [get_ports led[0]]
set_property PACKAGE_PIN T21 [get_ports led[1]]
set_property PACKAGE_PIN U22 [get_ports led[2]]
set_property PACKAGE_PIN U21 [get_ports led[3]]
set_property PACKAGE_PIN V22 [get_ports led[4]]
set_property PACKAGE_PIN W22 [get_ports led[5]]
set_property PACKAGE_PIN U19 [get_ports led[6]]
set_property PACKAGE_PIN U14 [get_ports led[7]]

set_property IOSTANDARD LVCMOS33 [get_ports led]

set_property PACKAGE_PIN W8 [get_ports cmv_clk]
set_property PACKAGE_PIN V10 [get_ports cmv_t_exp1]
set_property PACKAGE_PIN V9 [get_ports cmv_t_exp2]
set_property PACKAGE_PIN V8 [get_ports cmv_frame_req]

set_property IOSTANDARD LVCMOS33 [get_ports cmv_*]



set_property PACKAGE_PIN L19 [get_ports cmv_lvds_clk_n]
set_property PACKAGE_PIN L18 [get_ports cmv_lvds_clk_p]

set_property PACKAGE_PIN C19 [get_ports cmv_lvds_outclk_n]
set_property PACKAGE_PIN D18 [get_ports cmv_lvds_outclk_p]

set_property IOSTANDARD LVDS_25 [get_ports cmv_lvds_*]

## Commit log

2013-06-06 Initial Commit of SFE Files (schematic and PCB layout)
2013-06-06 updated readme.txt
2013-06-11 some progress with GND plane connections and a couple of capacitors routed
2013-06-12 contact info updated
2013-06-12 added axiom alpha nikon lens f-mount mechanical drawings
2013-06-18 more PCB routing progress
    added CMV12000 chip size
    added pcb to lens mount screw holes
    some problems fixed
    board size slightly increased to accomodate screw holes for lens mount
    more capacitors routed
2013-06-18 more PCB progress
    some more capacitors placed and routed
2013-06-18 added space constraints documentation
2013-06-18 preliminary CMV12000 KiCad Component (WIP)
2013-06-18 minor board size tweaks - still needs fixing
2013-06-18 all parts placed and routed
2013-06-18 updated todos
2013-06-21 3.3v supply plane and connections done
2013-06-21 finished 3.0V and 1.8V power planes, added voltage area overview PSD
2013-06-22 added power planes jpg
2013-06-23 added Zedboard related files for TFTP booting
2013-06-24 updates, fixes, improvements
2013-06-26 more PCB routing progress
2013-06-26 again more PCB updates
2013-07-01 added CMV12000 datasheet
2013-07-01 more progress
2013-07-08 pmod led matrix hardware added
2013-07-11 lots of updates
2013-07-11 eagle library added (FMC connector and Cmosis CMV12000)
2013-07-12 version 0.8 of the SFE PCB now complete - ready for review/eror checking
2013-07-12 added FMC datasheets
2013-07-12 added cmv12000 operation mode note
2013-08-21 Version 0.9 of the PCB board layout
2013-08-24 V1.0 commited
2013-08-24 folder clean up
2013-09-26 Added scripts
2013-09-26 more scripts
2013-09-26 some restructuring
2013-10-28 updated to version 1.1, added bom, gerber, etc
2013-12-05 obsolete, can now be found in alpha-software
2013-12-05 moved files into subdirectory based on version
2013-12-05 removed old files now in cmv12k-adapter-v1.1
2014-01-22 updated image sensor datasheet
2014-04-01 1D 4K Paddle Schematic and Board Layout
2014-04-01 Added Copyright, License and Frame
2014-04-01 Added the PaddleBox.eps
2014-06-10 3D CAD file of lens mount parts
